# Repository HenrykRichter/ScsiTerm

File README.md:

# SCSITerm 08-15 

This project is a design of an active SCSI terminator for DB-25 ports.

## Pictures

The picture below shows Revision3 of the board.

## Parts list
- 1  DB-25 male (solder cup)
- 1  Voltage regulator SOT-223 LD1117 SC-R (or similar)
- 18 Resistors 110R 0805
- 1  Resistor 680R 0805 (R19, optional)
- 1  LED 0805 (optional)
- 3  Capacitors 10uF 0805
- 1  Resistor 220R 0805 (R21)
- 1  Resistor 330R 0805 (R20)
- 1  Resistor 2k 0805 (C3, instead of a previously planned capacitor for accurate 2.85V)

## Building and installation notes
Soldering should be straightforward for the SMD components and the DB-25 connector. Please don't forget the resistors on the underside of the PCB.

The PCB was designed with typical DB-25 shells in mind to be used as enclosure. Nevertheless, a custom case design for 3D printing is part of the repository. Just print the design twice and fasten it using M2.5 x 10 cylindrical screws and matching nuts.

## License

The material in this project may be used under the terms of the Attribution-NonCommercial-ShareAlike 4.0 International creative commons license. Please refer to https://creativecommons.org/licenses/by-nc-sa/4.0/ for details or see the LICENSE file in this repository.

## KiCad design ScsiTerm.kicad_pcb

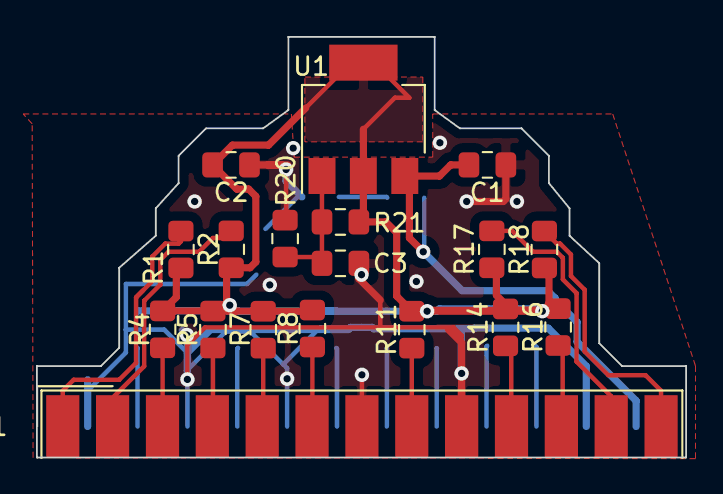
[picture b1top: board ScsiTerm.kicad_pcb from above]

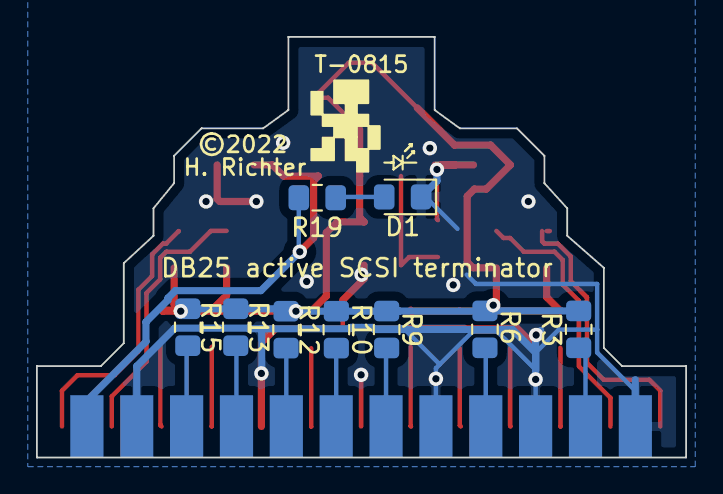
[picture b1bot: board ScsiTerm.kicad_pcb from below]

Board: 2 copper layers, 36.1 x 23.4 mm, 27 parts (9 on the bottom side), 23 nets.

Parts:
C1, C2: 10uF; C_0805_2012Metric_Pad1.15x1.40mm_HandSolder
C3: 4.7uF; C_0805_2012Metric_Pad1.15x1.40mm_HandSolder
D1: LED; LED_0805_2012Metric_Pad1.15x1.40mm_HandSolder
J1: DB25_Male; DSUB-25_Male_EdgeMount_P2.77mm
R1, R2, R3, R4, R5, R6, R7, R8, R9, R10, R11, R12, R13, R14, R15, R16, R17, R18: 110; R_0805_2012Metric_Pad1.15x1.40mm_HandSolder
R19: 680; R_0805_2012Metric_Pad1.15x1.40mm_HandSolder
R20: 150; R_0805_2012Metric_Pad1.15x1.40mm_HandSolder
R21: 120; R_0805_2012Metric_Pad1.15x1.40mm_HandSolder
U1: LD1117 SC-R; SOT-223-3_TabPin2

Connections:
+5V: C1.1, J1.25, R19.2, U1.3
/2.85V: C2.1, R1.1, R2.1, R3.1, R4.1, R5.1, R6.1, R7.1, R8.1, R9.1, R10.2, R11.2, R12.2, R13.2, R14.2, R15.2, R16.2, R17.2, R18.2, R21.2, U1.2
/ACK: J1.5, R7.2
/ATN: J1.17, R6.2
/BSY: J1.6, R8.2
/C_D: J1.15, R3.2
/DB0: J1.8, R11.1
/DB1: J1.21, R12.1
/DB2: J1.22, R13.1
/DB3: J1.10, R14.1
/DB4: J1.23, R15.1
/DB5: J1.11, R16.1
/DB6: J1.12, R17.1
/DB7: J1.13, R18.1
/DBP: J1.20, R10.1
/I_O: J1.3, R4.2
/MSG: J1.2, R2.2
/REQ: J1.1, R1.2
/RST: J1.4, R5.2
/SEL: J1.19, R9.2
GND: C1.2, C2.2, C3.2, D1.1, J1.7, J1.9, J1.14, J1.16, J1.18, J1.24, R20.1
unnamed: C3.1, R20.2, R21.1, U1.1
unnamed: D1.2, R19.1

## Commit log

2021-12-26 initial Git import
2021-12-26 added pictures
2022-10-08 Version 0.3: 2.85V regulator by adjustable variant This version will now use a more common voltage regulator since the 2.85V parts are going EOL.
2022-10-08 Updated Readme, added 0.3 picture

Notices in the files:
ScsiTerm.kicad_pcb:
©2022
